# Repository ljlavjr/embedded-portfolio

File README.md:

# Embedded Systems Portfolio

## About Me
My name is Lawrence (Larry) Lavigne. I am a Computer Engineering graduate from the University of Tennessee, Knoxville, and I work as an Embedded Software Engineer. This portfolio is where I continue building on the fundamentals I learned at UT and expand into areas of embedded systems beyond what I touch day-to-day at work: bare-metal firmware, RTOS, automotive protocols, custom PCB design, and eventually RF and hardware security.

## What This Is
This is a collection of projects that build from the "Hello World" of embedded programming, blinking an LED, through custom PCB design, embedded Linux, and network security. Each new project builds on what the previous ones have taught me.

## Projects

### Phase 1: AVR Bare-Metal
| # | Project | Platform | Skills | Status |
|---|---------|----------|--------|--------|
| 01 | Bare-Metal Blink | ATmega2560 | Registers, Makefiles, Toolchain | Complete |
| 02 | UART Driver | ATmega2560 | Polling, Serial, Driver Architecture | Complete |
| 03 | Interrupt UART | ATmega2560 | ISR, Ring Buffer, Volatile | Complete |
| 04 | Multi-Sensor Polling | ATmega2560 | ADC, Super-loop Pain | Complete |

### Phase 2: STM32 Bare-Metal
| # | Project | Platform | Skills | Status |
|---|---------|----------|--------|--------|
| 05 | Bare-Metal Startup | STM32F407 | ARM Startup, Linker Scripts, Vector Table | Complete |
| 06 | Custom HAL | STM32F407 | GPIO, UART, SPI Drivers, Abstraction | Complete |
| 07 | DMA Data Acquisition | STM32F407 | DMA, ADC, Double Buffering | Complete |

### Phase 3: RTOS
| # | Project | Platform | Skills | Status |
|---|---------|----------|--------|--------|
| 08 | FreeRTOS Basics | STM32F407 | Tasks, Priorities, Scheduler | Complete |
| 09 | Inter-Task Communication | STM32F407 | Queues, Producer-Consumer | Complete |
| 10 | Resource Sharing | STM32F407 | Mutexes, Semaphores, Priority Inversion | Complete |
| 11 | Real-Time Sensor System | STM32F407 | Multi-task Application, Timing Analysis | Complete |

### Phase 4: Automotive Protocols
| # | Project | Platform | Skills | Status |
|---|---------|----------|--------|--------|
| 12 | CAN Bus Communication | STM32F407 | CAN Protocol, Message Filtering, Multi-node | Complete |
| 13 | Modbus RTU | STM32F407 | Industrial Protocol, Master/Slave, CRC | Planned |
| 14 | OBD-II Reader | STM32F407 | Automotive Diagnostics, CAN, PID Parsing | Planned |

### Phase 4.5: Custom Hardware
| # | Project | Platform | Skills | Status |
|---|---------|----------|--------|--------|
| 12b | CAN Node PCB | Custom STM32 | KiCad, Schematic Capture, 2-layer Layout | Planned |
| 13b | RS-485 Modbus PCB | Custom STM32 | Differential Signaling, Transceiver Design | Planned |

### Phase 5: Firmware Fundamentals
| # | Project | Platform | Skills | Status |
|---|---------|----------|--------|--------|
| 15 | Watchdog Recovery | STM32F407 | IWDG, Fault Logging, Safe State | Complete |
| 16 | Custom Bootloader | STM32F407 | Dual-bank Flash, Jump to App, Update Protocol | Planned |
| 17 | USB CDC Device | STM32F407 | USB Stack, Descriptors, Enumeration | Planned |

### Phase 6: IoT & Wireless
| # | Project | Platform | Skills | Status |
|---|---------|----------|--------|--------|
| 18 | MQTT Sensor Node | ESP32 | WiFi, MQTT, JSON, Sleep Modes | Planned |
| 19 | Motion Detection Camera | ESP32-CAM | Camera Interface, Image Processing, Alerts | Planned |
| 20 | BLE + WiFi Gateway | Arduino Uno R4 WiFi | Multi-protocol, Bridging, FreeRTOS | Planned |
| 21 | OTA Update System | Arduino Uno R4 WiFi | Bootloaders, Flash Management, Verification | Planned |

### Phase 7: Embedded Linux
| # | Project | Platform | Skills | Status |
|---|---------|----------|--------|--------|
| 22 | PRU Real-Time Control | BeagleBone Black | PRU Assembly, Shared Memory, Hard Real-time | Planned |
| 23 | Linux Kernel Driver | BeagleBone Black | Kernel Modules, Character Devices, sysfs | Planned |
| 24 | Device Tree Overlays | BeagleBone Black | Device Tree, Hardware Description | Planned |
| 25 | Custom Yocto Image | Raspberry Pi Zero 2W | Build Systems, Cross-compilation | Planned |

### Phase 8: Networking & Security
| # | Project | Platform | Skills | Status |
|---|---------|----------|--------|--------|
| 26 | Secure Bootloader | STM32F407 | Cryptographic Verification, Secure Boot | Planned |
| 27 | Encrypted MQTT | ESP32 | TLS, Certificates, Secure Communication | Planned |
| 28 | Network Packet Analyzer | BeagleBone Black | Raw Sockets, Protocol Parsing, Filtering | Planned |
| 29 | Embedded Firewall | Raspberry Pi Zero 2W | iptables, Traffic Rules, Logging | Planned |

### Infrastructure
| # | Project | Platform | Skills | Status |
|---|---------|----------|--------|--------|
| -- | CI/CD Pipeline | Raspberry Pi 4 | GitHub Actions, Self-hosted Runner | Complete |
| -- | IoT Backend | Raspberry Pi 4 | MQTT, InfluxDB, Grafana, Telegraf | Complete |

## Learning Path
I'm taking a bottom-up approach. Starting with bare-metal AVR and ARM programming to build hardware fundamentals (registers, GPIOs, data transfer), then moving to FreeRTOS since RTOS experience appears in nearly every embedded job posting. From there I branch into automotive protocols (CAN, Modbus) since I have some experience in that field, then move firmware projects onto custom PCBs I design in KiCad. After that comes IoT and wireless work, with a long-term direction toward RF systems and hardware security (both offensive and defensive). I also set up a CI/CD pipeline from GitHub Actions to my Raspberry Pi server for build visibility after each push.

## Hardware
- Arduino Mega 2560 (Elegoo)
- STM32F407G-DISC1
- Raspberry Pi 4 (CI/CD server, IoT backend)
- others added as we progress through the list

## Infrastructure
- Self-hosted GitHub Actions runner on Pi 4
- MQTT broker + InfluxDB + Grafana for IoT projects

## Resources
- [ATmega2560 Datasheet](https://ww1.microchip.com/downloads/en/devicedoc/atmel-2549-8-bit-avr-microcontroller-atmega640-1280-1281-2560-2561_datasheet.pdf)
- [STM32F407 Reference Manual](https://www.st.com/resource/en/reference_manual/rm0090-stm32f405415-stm32f407417-stm32f427437-and-stm32f429439-advanced-armbased-32bit-mcus-stmicroelectronics.pdf)
- [STM32F407G-DISC1 User Manual](https://www.st.com/resource/en/user_manual/um1472-discovery-kit-with-stm32f407vg-mcu-stmicroelectronics.pdf)
- [FreeRTOS Documentation](https://www.freertos.org/Documentation/RTOS_book.html)

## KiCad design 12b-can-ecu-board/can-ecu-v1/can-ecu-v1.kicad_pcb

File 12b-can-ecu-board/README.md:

# Project 12b: Custom CAN ECU Board

## Purpose
A custom STM32 based ECU board that connects to a CAN bus and performs configurable actions (LED patterns, fan control, button input reporting) based on received messages. Designed to be a second node on the bus alongside my STM32F407 Discovery board for two node CAN demonstrations.

## Functional Requirements
1. Receive and transmit CAN messages at 125, 250, 500, and 1000 kbps
2. Drive 4 status LEDs with patterns controlled by CAN messages
3. Drive 1 PWM output at 5V via MOSFET, controlled by CAN messages
4. Read 2 button inputs and report state changes over CAN
5. Read 1 analog input (potentiometer) and report value periodically over CAN
6. Provide power and CAN activity indicator LEDs
7. Allow programming and debugging via 5 pin SMT SWD header
8. Allow UART debug via 4 pin SMT UART header
9. Operate from USB-C 5V power only

## Non Functional Requirements
1. 2 layer PCB
2. 100% SMT components, full assembly via JLCPCB
3. Maximum dimensions: 80mm x 60mm
4. Cost target: under $20 per board (5 board run)
5. All parts available in JLCPCB parts library where possible

## Out of Scope for v1
1. 12V automotive style input (USB-C only for now)
2. Automotive grade transient protection (TVS arrays, common mode chokes)
3. CAN FD support
4. Galvanic isolation
5. Full size USB to UART bridge (use external FTDI cable)

## Bill of Materials

| # | Part | Manufacturer | JLC Part | Library | Approx Cost | Package | Notes |
|---|------|--------------|----------|---------|-------------|---------|-------|
| 1 | STM32F407VGT6 | ST | C18584 | Extended | $9.00 | LQFP-100 | Same as Discovery |
| 2 | AMS1117-3.3 | EVVO | C6186 | Basic | $0.10 | SOT-223-3L | 3.3V LDO |
| 3 | SN65HVD230D | TI | C12084 | Extended | $1.50 | SOIC-8 | CAN transceiver |
| 4 | USB4135-GF-A | GCT | C2765186 | Extended | $0.78 | SMT horizontal | USB-C power only |
| 5 | LMT86DCKR | TI | (extended) | Extended | $1.00 | SC70-5 | Analog temp sensor |
| 6 | 8MHz 20pF crystal | YXC | C115962 | Extended | $0.20 | SMD-3225 | HSE for STM32 |
| 7 | 20pF 0603 C0G | UNIOHM | C1804 | Basic | $0.02 | 0603 | 2x for crystal load caps |
| 8 | SI2302 | various | C10487 | Basic | $0.04 | SOT-23 | N-channel logic level MOSFET |
| 9 | 1N5819 Schottky | various | C8598 | Basic | $0.02 | SOD-123 | Fan flyback diode |
| 10 | TS-1187A SMT button | various | C318884 | Basic | $0.10 | SMT 6mm | 3x: 2 user + 1 reset |
| 11 | LED Red 0603 | KENTO | C2286 | Basic | $0.05 | 0603 | 2x: power, CAN active |
| 12 | LED Green 0603 | KENTO | C72043 | Basic | $0.05 | 0603 | 2x output |
| 13 | LED Blue 0603 | KENTO | C72041 | Basic | $0.05 | 0603 | 1x output |
| 14 | LED Yellow 0603 | KENTO | C72038 | Basic | $0.05 | 0603 | 1x output |
| 15 | 470Ω 0603 1% | UNIOHM | C23179 | Basic | $0.01 | 0603 | 6x for LEDs |
| 16 | 5.1kΩ 0603 1% | UNIOHM | C23186 | Basic | $0.01 | 0603 | 2x USB-C CC pins |
| 17 | 10kΩ 0603 1% | UNIOHM | C25804 | Basic | $0.01 | 0603 | MOSFET pull down + boot pin + reset |
| 18 | 100Ω 0603 1% | UNIOHM | C22775 | Basic | $0.01 | 0603 | MOSFET gate series |
| 19 | 0.1µF 0603 X7R | various | C14663 | Basic | $0.01 | 0603 | ~12x decoupling |
| 20 | 10µF 0805 X5R | various | C15850 | Basic | $0.03 | 0805 | 2x bulk caps |
| 21 | 0.1 inch male header | various | C124378 | Extended | $0.20 | THT | 4x: SWD, UART, CAN, fan |

## Note
The board will be assembled by JLCPCB since I do not own a soldering station :(

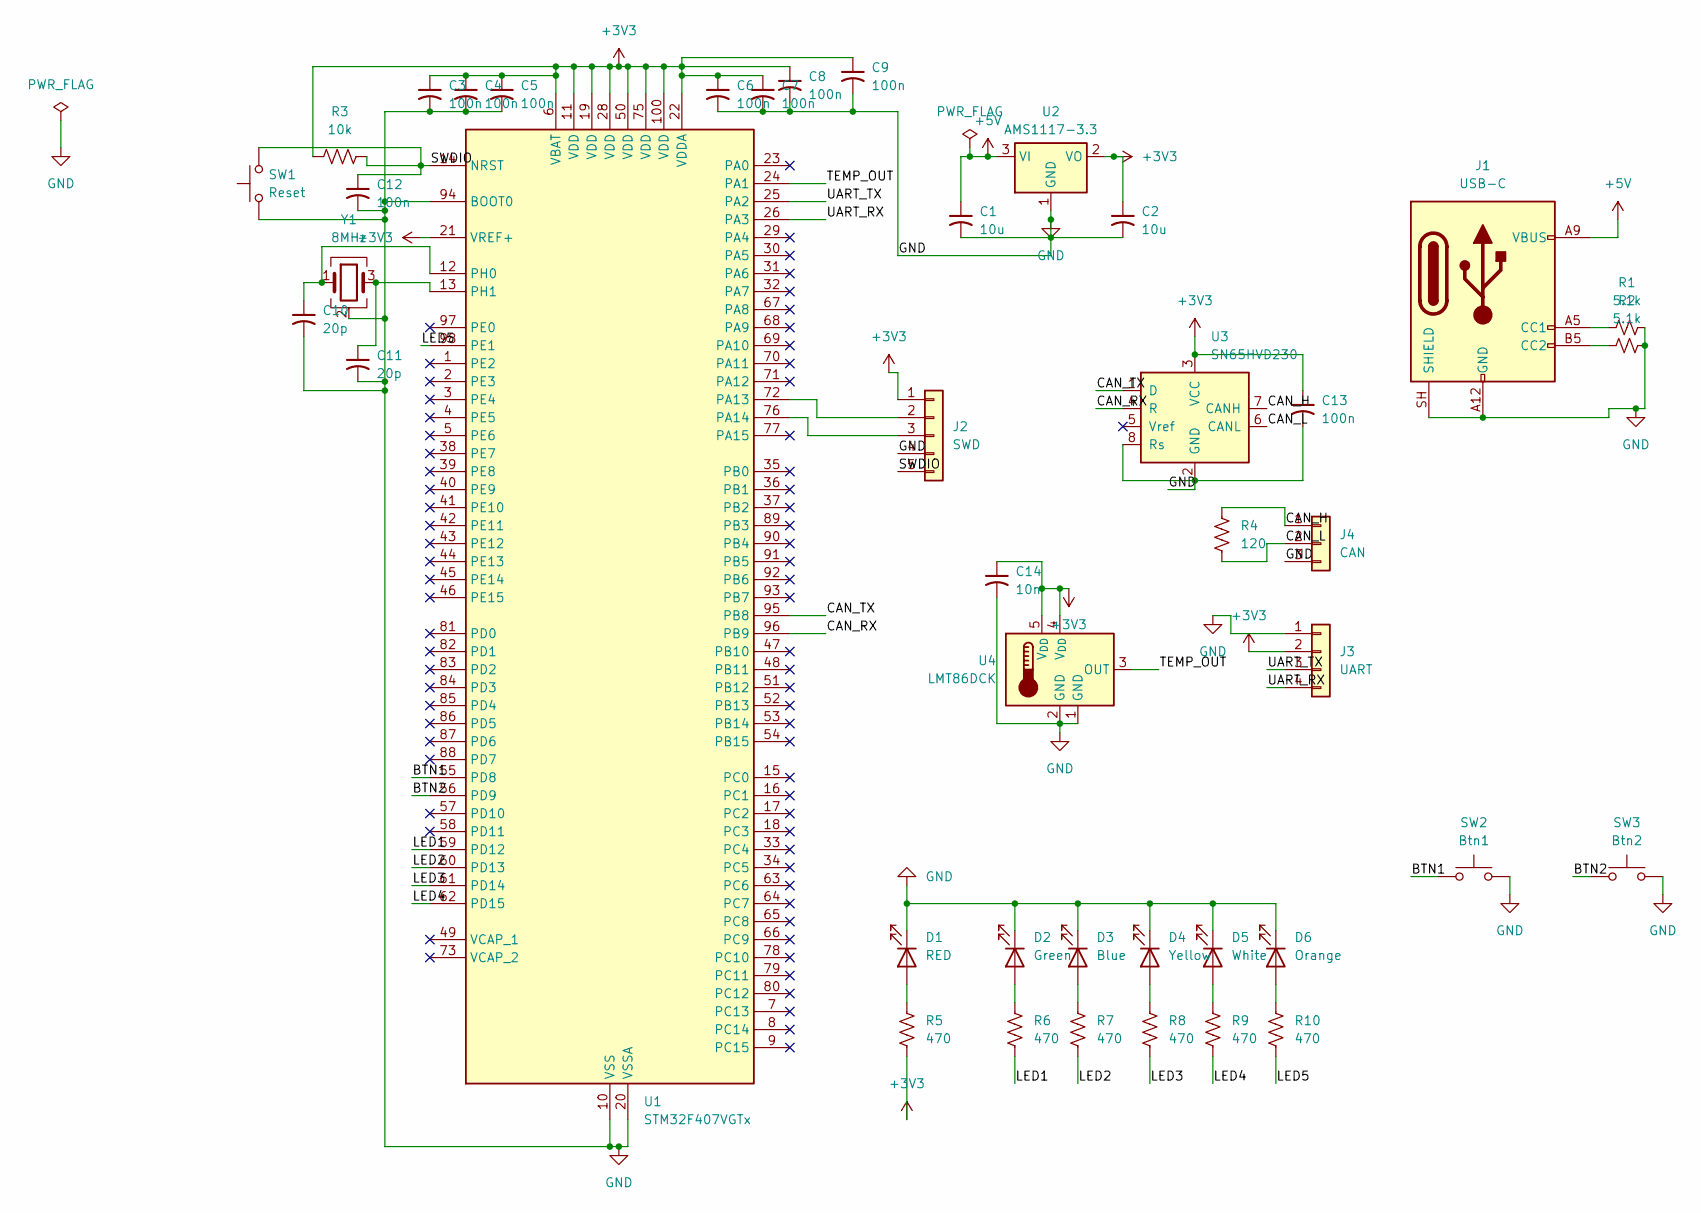
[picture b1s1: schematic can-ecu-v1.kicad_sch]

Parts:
C1, C2: 10u; C_0603_1608Metric; LCSC C19702
C3, C4, C5, C6, C7, C8, C9, C12, C13: 100n; C_0603_1608Metric; LCSC C14663
C10, C11: 20p; C_0603_1608Metric; LCSC C1804
C14: 10n; C_0603_1608Metric; LCSC C57112
D1: RED; LED_0603_1608Metric; LCSC C2286
D2: Green; LED_0603_1608Metric; LCSC C72043
D3: Blue; LED_0603_1608Metric; LCSC C72041
D4: Yellow; LED_0603_1608Metric; LCSC C72038
D5: White; LED_0603_1608Metric; LCSC C2290
D6: Orange; LED_0603_1608Metric; LCSC C12624
J1: USB-C; USB_C_Receptacle_GCT_USB4135-GF-A_6P_TopMnt_Horizontal; LCSC C2765186
J2: SWD; PinHeader_1x05_P2.54mm_Vertical; LCSC C50982
J3: UART; PinHeader_1x04_P2.54mm_Vertical; LCSC C50981
J4: CAN; PinHeader_1x03_P2.54mm_Vertical; LCSC C50980
R1, R2: 5.1k; R_0603_1608Metric; LCSC C23186
R3: 10k; R_0603_1608Metric; LCSC C25804
R4: 120; R_0603_1608Metric; LCSC C22787
R5, R6, R7, R8, R9, R10: 470; R_0603_1608Metric; LCSC C23179
SW1: Reset; SW_SPST_PTS645Sx43SMTR92; LCSC C318884
SW2: Btn1; SW_SPST_PTS645Sx43SMTR92; LCSC C318884
SW3: Btn2; SW_SPST_PTS645Sx43SMTR92; LCSC C318884
U1: STM32F407VGTx; LQFP-100_14x14mm_P0.5mm; LCSC C12345
U2: AMS1117-3.3; SOT-223-3_TabPin2; LCSC C6186
U3: SN65HVD230; SOIC-8_3.9x4.9mm_P1.27mm; LCSC C12084
U4: LMT86DCK; SOT-353_SC-70-5; LCSC C133909
Y1: 8MHz; Crystal_SMD_3225-4Pin_3.2x2.5mm; LCSC C115962

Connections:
+3V3: C2.1, C3.1, C4.1, C5.1, C6.1, C7.1, C8.1, C9.1, C13.1, C14.1, J2.1, J3.2, R3.1, R5.2, U1.6 (VBAT), U1.11 (VDD), U1.19 (VDD), U1.21 (VREF+), U1.22 (VDDA), U1.28 (VDD), U1.50 (VDD), U1.75 (VDD), U1.100 (VDD), U2.2 (VO), U3.3 (VCC), U4.4 (V_{DD}), U4.5 (V_{DD})
+5V: C1.1, J1.A9 (VBUS), J1.B9 (VBUS), U2.3 (VI)
/BTN1: SW2.1, U1.55 (PD8)
/BTN2: SW3.1, U1.56 (PD9)
/CAN_H: J4.1, R4.1, U3.7 (CANH)
/CAN_L: J4.2, R4.2, U3.6 (CANL)
/CAN_RX: U1.96 (PB9), U3.4 (R)
/CAN_TX: U1.95 (PB8), U3.1 (D)
/LED1: R6.2, U1.59 (PD12)
/LED2: R7.2, U1.60 (PD13)
/LED3: R8.2, U1.61 (PD14)
/LED4: R9.2, U1.62 (PD15)
/LED5: R10.2, U1.98 (PE1)
/SWDIO: C12.1, J2.5, R3.2, SW1.2, U1.14 (NRST)
/TEMP_OUT: U1.24 (PA1), U4.3 (OUT)
/UART_RX: J3.4, U1.26 (PA3)
/UART_TX: J3.3, U1.25 (PA2)
GND: C1.2, C2.2, C3.2, C4.2, C5.2, C6.2, C7.2, C8.2, C9.2, C10.2, C11.2, C12.2, C13.2, C14.2, D1.1 (K), D2.1 (K), D3.1 (K), D4.1 (K), D5.1 (K), D6.1 (K), J1.A12 (GND), J1.B12 (GND), J1.SH (SHIELD), J2.4, J3.1, J4.3, R1.2, R2.2, SW1.1, SW2.2, SW3.2, U1.10 (VSS), U1.20 (VSSA), U1.27 (VSS), U1.74 (VSS), U1.94 (BOOT0), U1.99 (VSS), U2.1 (GND), U3.2 (GND), U3.8 (Rs), U4.1 (GND), U4.2 (GND), Y1.2 (G), Y1.4 (G)
unnamed: D1.2 (A), R5.1
unnamed: D2.2 (A), R6.1
unnamed: D3.2 (A), R7.1
unnamed: D4.2 (A), R8.1
unnamed: D5.2 (A), R9.1
unnamed: D6.2 (A), R10.1
unnamed: J1.A5 (CC1), R1.1
unnamed: J1.B5 (CC2), R2.1
unnamed: J2.2, U1.72 (PA13)
unnamed: J2.3, U1.76 (PA14)
unnamed: C10.1, U1.12 (PH0), Y1.1
unnamed: C11.1, U1.13 (PH1), Y1.3

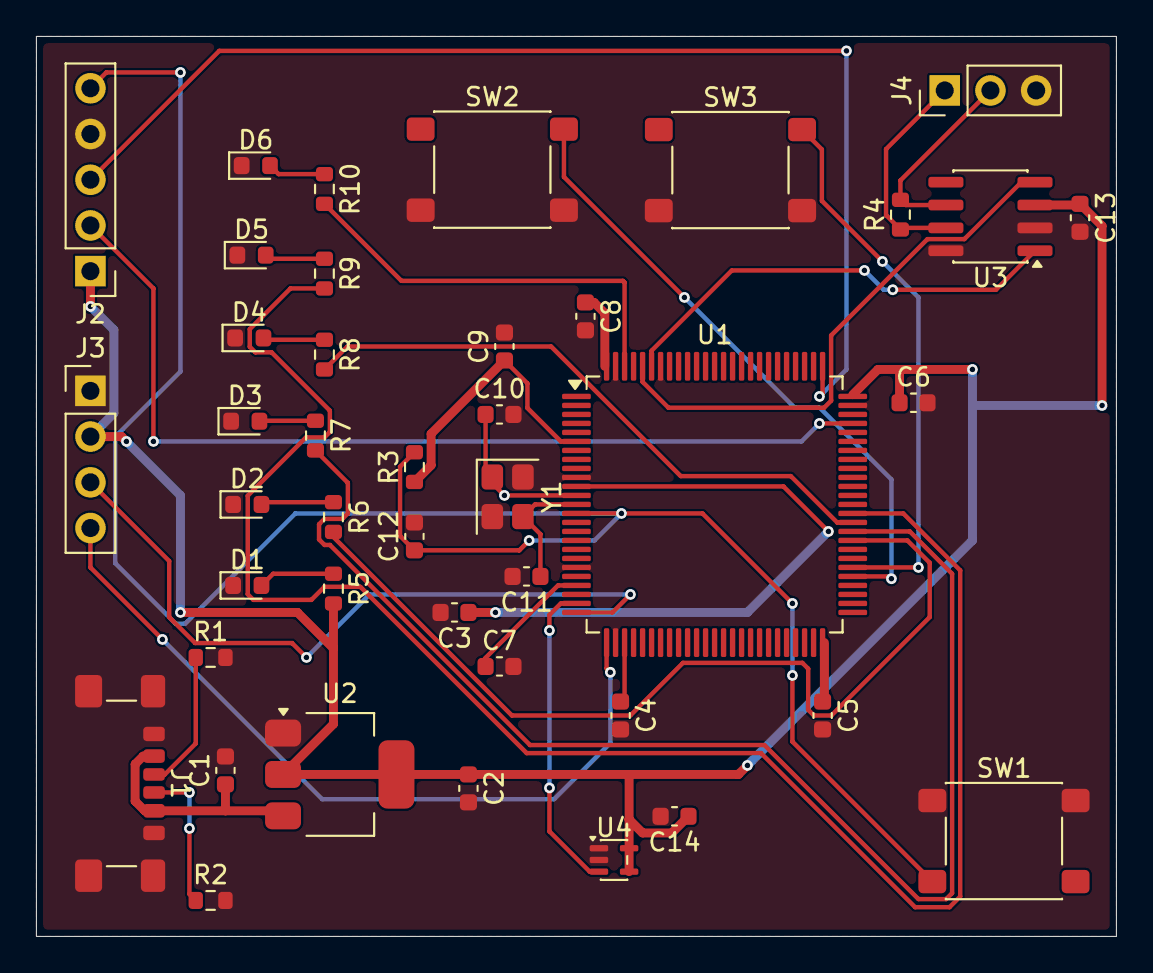
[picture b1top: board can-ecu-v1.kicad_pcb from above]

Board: 2 copper layers, 60.0 x 50.0 mm, 42 parts (0 on the bottom side), 30 nets.

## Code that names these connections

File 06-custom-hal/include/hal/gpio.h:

#ifndef GPIO_H
#define GPIO_H

#include "stm32f407.h"

typedef enum {
    GPIO_MODE_INPUT = 0,      // 00
    GPIO_MODE_OUTPUT = 1,     // 01
    GPIO_MODE_ALT = 2,        // 10
    GPIO_MODE_AN = 3          // 11
} GPIO_MODE;

typedef enum {
    GPIO_OUTTYPE_PUSHPULL,
    GPIO_OUTTYPE_OPENDRAIN
} GPIO_OUTPUT_TYPE;

typedef enum {
    GPIO_SPEED_LOW,
    GPIO_SPEED_MEDIUM,
    GPIO_SPEED_HIGH,
    GPIO_SPEED_VHIGH
} GPIO_SPEED;

typedef enum {
    GPIO_PULL_UD_NOPUPD,
    GPIO_PULL_UD_PULLU,
    GPIO_PULL_UD_PULLD
} GPIO_PULL_UD;

#define HIGH 1
#define LOW 0

#define PA2 2   // GPIOA Pin 2
#define PA3 3   // GPIOA Pin 3
#define PA5 5   // GPIOA Pin 5
#define PA6 6   // GPIOA Pin 6
#define PA7 7   // GPIOA Pin 7


#define PD12 12 // GPIOD Pin 12 (Green LED)
#define PD13 13 // GPIOD Pin 13 (Orange LED)
#define PD14 14 // GPIOD Pin 14 (Red LED)
#define PD15 15 // GPIOD Pin 15 (Blue LED)

void rcc_gpio_clock_enable(GPIO_TypeDef *port);
void gpio_init(GPIO_TypeDef *port, uint8_t pin, GPIO_MODE mode);
void gpio_set_otype(GPIO_TypeDef *port, uint8_t pin, GPIO_OUTPUT_TYPE otype);
void gpio_set_speed(GPIO_TypeDef *port, uint8_t pin, GPIO_SPEED speed);
void gpio_set_pull(GPIO_TypeDef *port, uint8_t pin, GPIO_PULL_UD pull);
void gpio_set_alt_func(GPIO_TypeDef *port, uint8_t pin, uint8_t function);
void write_pin(GPIO_TypeDef *port, uint8_t pin, uint32_t value);
uint8_t read_pin(GPIO_TypeDef *port, uint8_t pin);
void toggle_pin(GPIO_TypeDef *port, uint8_t pin);

#endif

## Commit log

2026-01-14 01-bare-metal-blink: initial AVR blink project
2026-01-14 01-bare-metal-blink: add README
2026-01-14 01-bare-metal-blink: updated README
2026-01-14 01-bare-metal-blink: update for ATmega2560
2026-01-14 01-bare-metal-blink: add memory map and clock system to README
2026-01-14 01-bare-metal-blink: fixed README
2026-01-19 02-uart-driver: Started uart project. Added uart.h and skeleton of uart.c.
2026-01-28 Add CI workflow
2026-01-28 02-uart-driver: Added main.c and Makefile to directory.
2026-01-29 02-uart-driver: initial UART driver
2026-01-29 02-uart-driver: add echo functionality
2026-01-29 02-uart-driver: debugging echo functionality
2026-01-29 02-uart-driver: debugging transmit
2026-01-29 02-uart-driver: working UART with echo test
2026-01-29 02-uart-driver: enabled own cli to turn on/off led
2026-01-29 03-uart-interrupt: modified code from 02-uart-driver to use interrupts while receiving from RX
2026-01-29 02-uart-driver: added a README.md
2026-01-30 03-uart-interrupt: Added README.md
2026-01-30 04-multi-sensor-polling: created adc driver code, setup makefile, set up main.c. Need to wire and test.
2026-01-30 CI: build all projects so far
2026-01-30 04-multi-sensor-polling: Added README.md
2026-02-02 Add portfolio README with project roadmap
2026-02-04 05-stm32-bare-metal: Created project for stm32 bare metal. Added Makefile and blank files for main, startup, and linker
2026-02-04 CI: updated build.yml to include 05-stm32-bare-metal
2026-02-04 05-stm32-bare-metal: Wrote linker.ld and startup.s
2026-02-04 CI: updated name of build workflow to 'Build Embedded Projects'
2026-02-05 Updated README.md project map to add Firmware projects
2026-02-05 05-stm32-bare-metal: Added blinking LED code to main.c
2026-02-05 05-stm32-bare-metal: Started README.md
2026-02-05 05-stm32-bare-metal: Finished README.md
2026-02-05 06-custom-hal: Initial commit. Created project file structure.
2026-02-05 06-custom-hal: defined our custom structs and pointers to gpio/rcc registers
2026-02-06 06-custom-hal: Added HAL functionality and main.c program to toggle led on and off using our new functions
2026-02-06 06-custom-hal: Updated README
2026-02-06 06-custom-hal: Added uart functionality
2026-02-06 06-custom-hal: Fixed Makefile to compile and use uart library
2026-02-06 06-custom-hal: Starting implementation of SPI
2026-02-07 06-custom-hal: trying to debug why screen not printing messages from uart
2026-02-07 06-custom-hal: Added spi functionality to the custom HAL
2026-02-07 Added SSI and SSM to spi.h. Seeing if it works correctly now
2026-02-07 06-custom-hal: working as intended. Updated README.md
2026-02-07 07-dma-data-acquisition: Set up the new project folder
2026-02-07 07-dma-acquisition: Implemented adc code
2026-02-07 07-dma-acauisition: ADC works. Changed gpio driver code to now call clock enable inside the gpio_init method like we do for uart_init. Keep it consistent.
2026-02-09 07-dma-data-acquisition: added dma driver files and some code. updated stm32 header file
2026-02-10 07-dma-acquisition: Added dma functionality. Updated Makefile and main README.md
2026-02-10 07-dma-acquisition: Added project README.md
2026-02-10 08-freeRTOS-basics: Initial commit
2026-02-13 08-freeRTOS-basics: created Makefile and FreeRTOSConfig.h
2026-02-13 08-freeRTOS-basics: fixing Makefile
2026-02-13 08-freeRTOS-basics: fixingFreeRTOSConfig.h
2026-02-13 08-freeRTOS-basics: fixing Makefile and FreeRTOSConfig.h
2026-02-13 08-freeRTOS-basics: Added Uart Task
2026-02-13 08-freeRTOS-basics: Added README.md and updated github workflow
2026-02-13 09-inter-task-comm: Initial commit
2026-02-13 Fixed github workflow
2026-02-13 09-inter-task-comm: Created main.c and added queue examples
2026-02-13 09-inter-task-comm: Created README.md
2026-02-15 08-freeRTOS-basics: debug
2026-02-15 08-freeRTOS-basics: Updated startup.s vector table section to include the specific handles we need for freeRTOS
2026-02-15 08-freeRTOS-basics: using hard faults to see what is not working
2026-02-15 08-freeRTOS-basics: Added enable_fpu call in startup.s to enable our FPU
2026-02-15 08-freeRTOS-basics: Working correctly now. Updated README.md to include and explain these necessary changes
2026-02-15 09-inter-task-comm: Updated startup.s and linker.ld to fix what broke in project 08
2026-02-15 Updated main README.md Project status
2026-02-15 10-resource-sharing: Initial commit. Created code to share resources
2026-02-15 10-resource-sharing: Using mutex instead of a binary semaphore
2026-02-15 10-resource-sharing: debugging hard fault
2026-02-15 10-resource-sharing: Fixed hard fault. Added README.md
2026-02-16 11-real-time-sensor-system: Initial commit
2026-02-16 11-real-time-sensor-system: Added timing driver code and set up tasks in our main.c without any work yet
2026-02-16 11-real-time-sensor-system: Added and updated adc driver code. Created tasks outlines and implemented the fast and slow sensor tasks
2026-02-17 11-real-time-sensor-system: added all tasks needed for this. onto testing
2026-02-17 11-real-time-sensor-system: updated makefile
2026-02-17 11-real-time-sensor-system: added #include FreeRTOS.h in timing.c
2026-02-17 11-real-time-sensor-system: added to FreeRTOSConfig.h and fixed linker.ld
2026-02-17 11-real-time-sensor-system: fixed jitter overflow
2026-02-17 11-real-time-sensor-system: fixed overflow
2026-02-17 11-real-time-sensor-system: added README.md
2026-02-17 11-real-time-sensor-system: fixed README.md
2026-02-18 15-watchdog-recovery: initial commit. copied over project 11 to new directory
2026-02-18 15-watchdog-recovery: created iwdg drivers. created main.c file for this project
2026-02-19 15-watchdog-recovery: added main.c comments
2026-02-19 15-watchdog-recovery: added fault injection into tasks. updated makefile
2026-02-19 15-watchdog-recovery: fixed missing } in main.c
2026-02-19 15-watchdog-recovery: fixing makefile
2026-02-19 15-watchdog-recovery: added event_groups.c to project from FreeRTOS source code
2026-02-19 Added to FreeRTOSConfig.h. Skeleton readme
2026-02-20 11-real-time-sensor-system: added gpio alt function mode so adc channel 0 can actaully work
2026-02-20 All driver code and makefile,linker,startup templates in one folder for easy copying to new projects
2026-03-26 Moving off computer
2026-04-19 15-watchdog-recovery: debugging code after long break
2026-04-19 15-watchdog-recovery: checking peripherals
2026-04-19 15-watchdog-recovery: testing RTOS task
2026-04-19 15-watchdog-recovery: testing RTOS task. this getting crazy
2026-04-19 15-watchdog-recovery: added timers
2026-04-19 15-watchdog-recovery: added queue in makefile
2026-04-19 15-watchdog-recovery: trying to run without watchdog
2026-04-19 15-watchdog-recovery: added back wathcdog
2026-04-19 15-watchdog-recovery: debugging watchdog
2026-04-19 15-watchdog-recovery: fixed the watchdog. IWDG SR loop was hanging
2026-04-29 12-can-bus-com: Added new project and updated rest of repo
2026-04-29 12-can-bus-com: fixed makefile issues and main issues
2026-04-29 12-can-bus-com: Added README.md
2026-05-27 12b-can-ecu-board: finished schematic
2026-05-28 12b-can-ecu-board: footprints assigned, LCSC numbers and values set
2026-05-30 12b-can-ecu-board: first attempt at the schematic. restarting bc errors
